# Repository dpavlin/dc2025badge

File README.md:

# DORS/CLUC Conference badge 2025

Conference page with badge instructions: [https://www.dorscluc.org/badge](https://www.dorscluc.org/badge/)

Build log: [https://hyperglitch.com/articles/dc2025-badge](https://hyperglitch.com/articles/dc2025-badge)

- `/hardware` - KiCad files for the badge
- `/firmware` - firmware for the badge
- `/3D` - 3D models for the stand, tag and programming jig
- `/notification_handler.py` - Python script for displaying the notifications and clock on the badge (in notifier mode)

----------------------------------------

This year’s badge has a number of functionalities, to be used both during and after the conference. During the conference the display can show your name (or any other text) and you also use it for quests. After the conference it can be used as a handy desktop notifier or a clock. And, of course, there’s a game available on it (not really Doom but it’s fast paced and action packed).

The badge contains a six character 9-segment display, logo shaped LED matrix, a NFC reader/writer, two buttons and a USB connection.

## How to set my own text?

The badge has six character alphanumeric display. It can show messages of up to 30 characters.

To set your custom text, hold the BTN1 for about three to five seconds until the badge switches to configuration mode. In that mode the BTN1 will move the cursor position while BTN2 will change the character under the cursor (hold it for fast character listing). To delete a character, select a space symbol (after number 9). To save the text hold the BTN1 again for three to five seconds until OK appears on screen.

## Quests? You said quests?

Yes! One is treasure hunt and another is badge hunt.

On the conference site there are nine hidden tags and your quest is to “collect” them all (tap them with your badge, please don’t physically take them). Each hidden tag will light up part of the logo on the badge. The first person who gets all of them will get a small reward.

Just like the last year’s badge which motivated attendants to interact with each other, this year’s badge also has an “interaction counter”. Put the antennas on two badges next to each other for a couple of seconds (it’s best to hold them both upwards and put antennas one over another so both screens could be seen) until both of them show the “NEW BADGE FOUND” text and they will exchange their details, incrementing the badge counter. NOTE: due to the power saving feature this might need to be repeated multiple times.

To check the current status of both quests press the BTN2 once or twice.

Note: in order to preserve the battery life, the NFC reader is in power save mode and it will activate when it detects a moving metal object nearby. Because of that sometimes it will be necessary to try the action (tapping the hidden tag or another badge) a couple of times.

## There are other modes?

I’m glad you asked. Yes, there are other modes on the badge:

- Conference mode scrolling text with quests)
- Clock (not really precise, needs configuration)
- Notifier (“passthrough” mode allowing you to set the screen over USB so it can be used as a desktop notifier)
- Game (a game!)
- Test (hardware test used during production)

To change the mode press and hold both buttons while powering on the badge. After a couple of seconds MODE will appear on screen. Use buttons to select the mode you like to try and press and hold both buttons for three to five seconds to confirm the selection.

## Configuration

When the badge is not in the notifier mode, some settings can be configured using the configuration menu available over USB connection. Connect the badge to computer (it probably won’t work on smartphone) and a new serial port will appear (/dev/ttyACM* on Linux, COM* on Windows). Connect to it either using some terminal program (miniterm, putty, screen, …) or even a web client such as the one available at https://www.anticyclone-systems.co.uk/aslwebterm.php (a Chromium based browser needs to be used as Firefox doesn’t support WebSerial). Make sure that Enter is set as CR+LF, click Connect and select your badge. Press Enter to redraw the menu. In case the Enter doesn’t work, try Ctrl+J.

## Notifier mode

When in notifier mode the serial terminal isn’t used for configuration but for the control. Each command must end ith a newline. Here are the commands:

- `S<some text>` will display that text on screen (for example “`Sshow this`”)
- `G<char_idx><segment_idx><1|0>` will control a specified character segment. `<char_idx>` is character index (0-5), `<segment_idx>` is the index of the segment (0-8) and `1|0` controls whether to turn the segment on or off. For example “`G161`” will turn on the middle horizontal segment on second character.
- `L<led_idx><1|0>` will turn the specified LED in the logo on or off. `<led_idx>` is in the range 00-39 (with leading zero). For example “`L021`” will turn on the led with index 2.
- `C` will clear the screen and LED matrix.
- `B<brightness>` will set the brightness where the `<brightness>` is in the rangge 00-99 (with leading zero). For example “`B05`” will set the brightness to 5%.

## License

ST middlewares and libraries are licensed under ST SLA0044 license. Shell menu is licensed under GPLv3. The rest of the code is licensed under MIT license.

The badge is designed by Igor Brkić from [https://hyperglitch.com](https://hyperglitch.com).

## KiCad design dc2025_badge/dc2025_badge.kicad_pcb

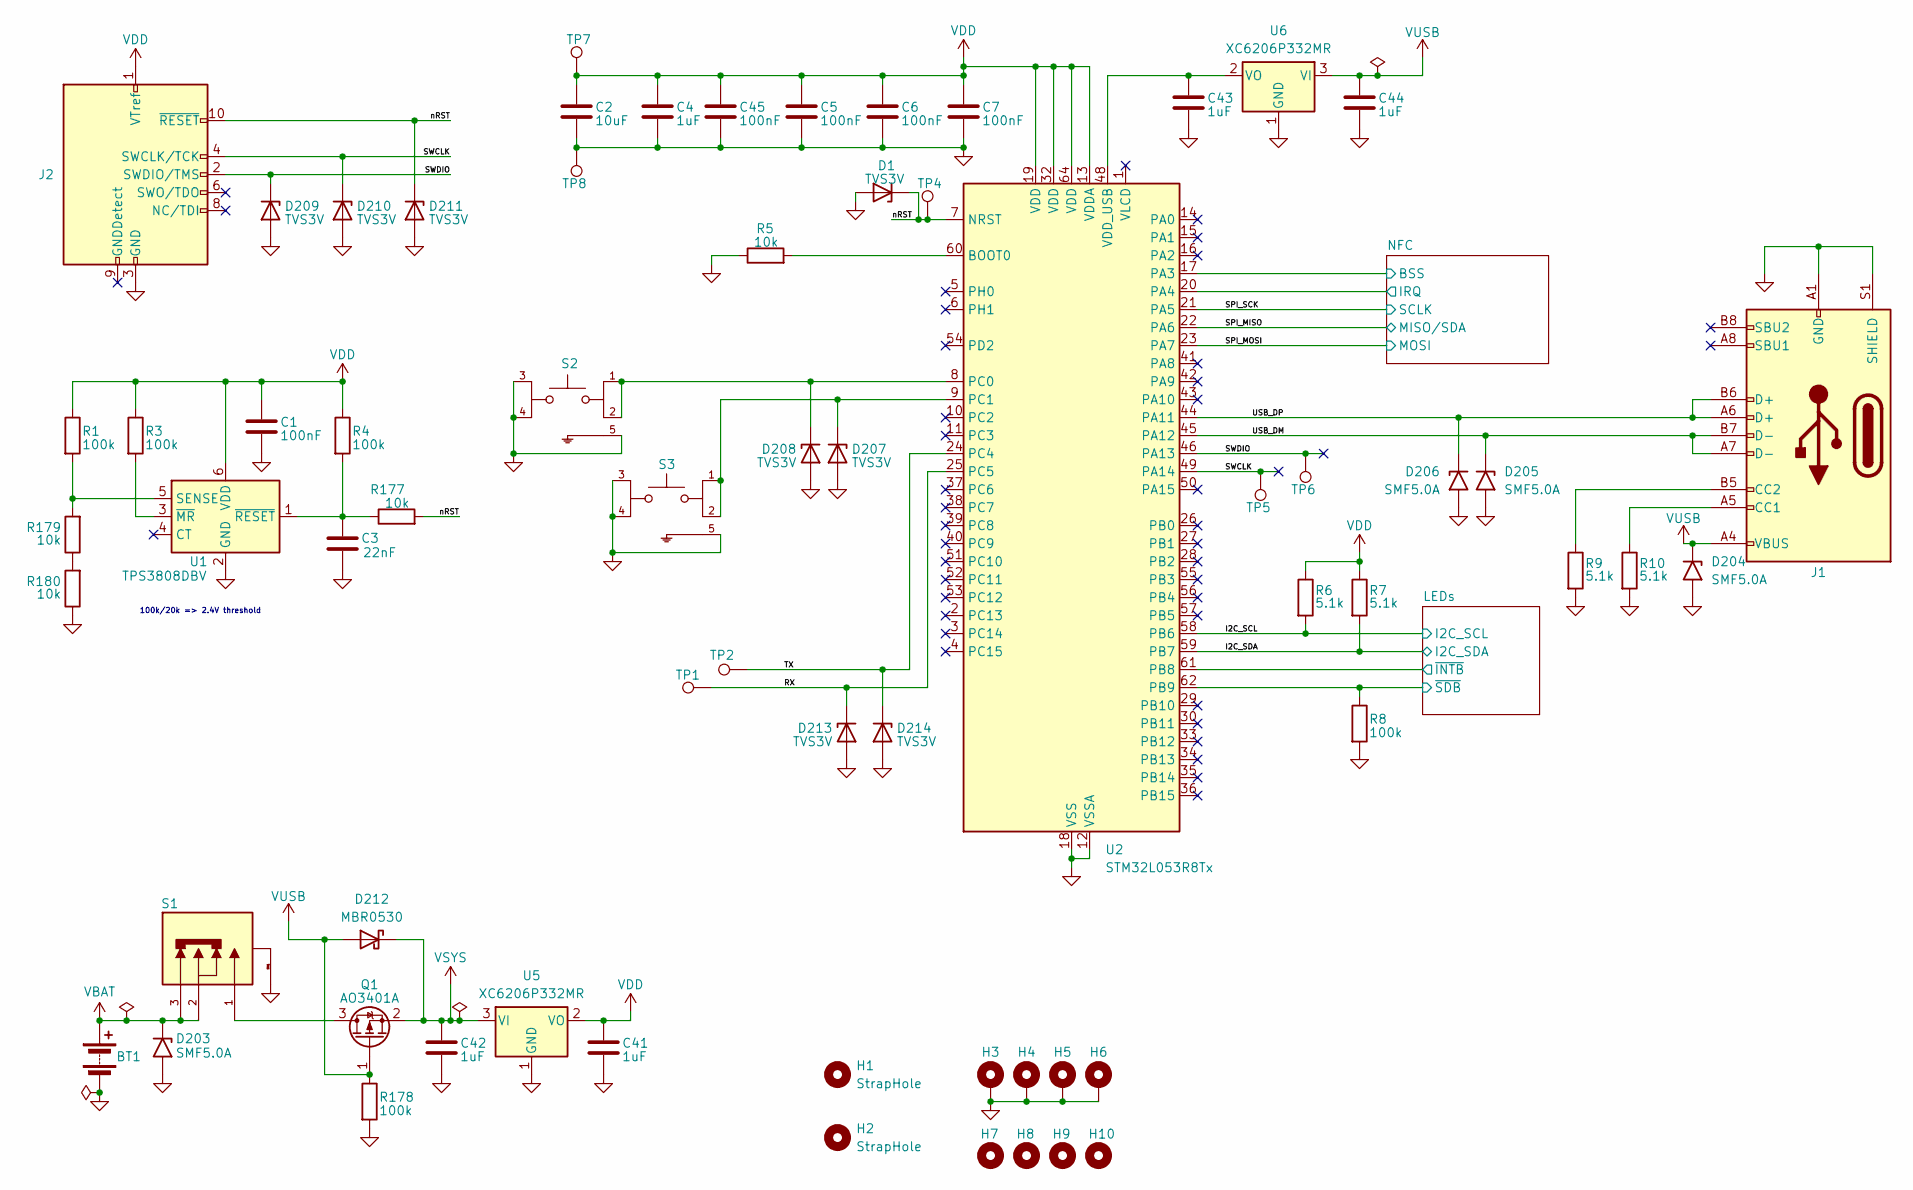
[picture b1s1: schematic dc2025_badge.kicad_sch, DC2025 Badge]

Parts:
BT1: Battery; keystone_2464
C1, C5, C6, C7, C45: 100nF; C_0402_1005Metric; MPN CL05B104KB54PNC; JLCPCB# C307331
C2: 10uF; C_0603_1608Metric; MPN GRM188Z71A106MA73D; JLCPCB# C237435
C3: 22nF; C_0402_1005Metric; MPN 0402B223K500NT; JLCPCB# C1532
C4, C41, C42, C43, C44: 1uF; C_0603_1608Metric; MPN 0603B105K250NT; JLCPCB# C59302
D1, D207, D208, D209, D210, D211, D213, D214: TVS3V; D_SOD-323; MPN SD03; JLCPCB# C502526
D203, D204, D205, D206: SMF5.0A; D_SMF; MPN SMF5.0A; JLCPCB# C19077497
D212: MBR0530; D_SOD-123; MPN MBR0530; JLCPCB# C475718
H1, H2: StrapHole; MountingHole_5mm
H3, H4, H5, H6: Cover nut; SMTSO3025CTJ; MPN C2916365; JLCPCB# C2916365
H7, H8, H9, H10: CoverMountingHole; MountingHole_3.2mm_M3_DIN965
J1: USB_C_Receptacle_USB2.0_16P; USB_C_Receptacle_GCT_USB4105-xx-A_16P_TopMnt_Horizontal; MPN TYPE-C-31-M-12; JLCPCB# C165948
J2: Conn_ARM_JTAG_SWD_10; Tag-Connect_TC2050-IDC-NL_2x05_P1.27mm_Vertical_with_bottom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
Q1: AO3401A; SOT-23; MPN AO3401A; JLCPCB# C15127
R1, R3, R4, R8, R178: 100k; R_0402_1005Metric; MPN 0402WGF1003TCE; JLCPCB# C25741
R5, R177, R179, R180: 10k; R_0402_1005Metric; MPN 0402WGF1002TCE; JLCPCB# C25744
R6, R7, R9, R10: 5.1k; R_0402_1005Metric; MPN 0402WGF5101TCE; JLCPCB# C25905
S1: SSSS811101; SW_SSSS811101; MPN SSSS811101; JLCPCB# C109335
S2, S3: SKHMQLE010; SW_SKHMQLE010; MPN SKHMQLE010; JLCPCB# C139767
TP1, TP2, TP4, TP5, TP6, TP7, TP8: TestPoint; TestPoint_Pad_D2.0mm
U1: TPS3808DBV; SOT-23-6; MPN TPS3808G01DBVR; JLCPCB# C19653
U2: STM32L053R8Tx; LQFP-64_10x10mm_P0.5mm; MPN STM32L053R8T6; JLCPCB# C79207
U5, U6: XC6206P332MR; SOT-23-3; MPN XC6206P332MR-G; JLCPCB# C5446

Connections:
/I2C_SCL: R6.2, U2.58 (PB6); also elsewhere on the board
/I2C_SDA: R7.2, U2.59 (PB7); also elsewhere on the board
/LEDs/~INTB: U2.61 (PB8); also elsewhere on the board
/LEDs/~SDB: R8.1, U2.62 (PB9); also elsewhere on the board
/NFC/BSS: U2.17 (PA3); also elsewhere on the board
/NFC/IRQ: U2.20 (PA4); also elsewhere on the board
/RX: D213.1 (K), TP1.1, U2.25 (PC5)
/SPI_MISO: U2.22 (PA6); also elsewhere on the board
/SPI_MOSI: U2.23 (PA7); also elsewhere on the board
/SPI_SCK: U2.21 (PA5); also elsewhere on the board
/SWCLK: D210.1 (K), J2.4 (SWCLK/TCK), TP5.1, U2.49 (PA14)
/SWDIO: D209.1 (K), J2.2 (SWDIO/TMS), TP6.1, U2.46 (PA13)
/TX: D214.1 (K), TP2.1, U2.24 (PC4)
/USB_DM: D205.1 (A1), J1.A7 (D-), J1.B7 (D-), U2.45 (PA12)
/USB_DP: D206.1 (A1), J1.A6 (D+), J1.B6 (D+), U2.44 (PA11)
/nRST: D1.1 (K), D211.1 (K), J2.10 (~RESET), R177.2, TP4.1, U2.7 (NRST)
GND: BT1.2 (-), C1.2, C2.2, C3.2, C4.2, C5.2, C6.2, C7.2, C41.2, C42.2, C43.2, C44.2, C45.2, D1.2 (A), D203.2 (A2), D204.2 (A2), D205.2 (A2), D206.2 (A2), D207.2 (A), D208.2 (A), D209.2 (A), D210.2 (A), D211.2 (A), D213.2 (A), D214.2 (A), H3.1, H4.1, H5.1, H6.1, J1.A1 (GND), J1.A12 (GND), J1.B1 (GND), J1.B12 (GND), J1.S1 (SHIELD), J2.3 (GND), J2.5 (GND), R5.1, R8.2, R9.2, R10.2, R178.2, R180.1, S1.SH1, S1.SH2, S1.SH3, S1.SH4, S2.3, S2.4, S2.5, S3.3, S3.4, S3.5, TP8.1, U1.2 (GND), U2.12 (VSSA), U2.18 (VSS), U2.31 (VSS), U2.47 (VSS), U2.63 (VSS), U5.1 (GND), U6.1 (GND); also elsewhere on the board
unnamed: D207.1 (K), S3.1, S3.2, U2.9 (PC1)
unnamed: D208.1 (K), S2.1, S2.2, U2.8 (PC0)
unnamed: J1.A5 (CC1), R10.1
unnamed: J1.B5 (CC2), R9.1
unnamed: Q1.3 (D), S1.1
unnamed: R179.1, R180.2
unnamed: R1.2, R179.2, U1.5 (SENSE)
unnamed: R3.2, U1.3 (~MR)
unnamed: C3.1, R4.2, R177.1, U1.1 (~RESET)
unnamed: R5.2, U2.60 (BOOT0)
unnamed: C43.1, U2.48 (VDD_USB), U6.2 (VO)
VBAT: BT1.1 (+), D203.1 (A1), S1.2, S1.3
VDD: C1.1, C2.1, C4.1, C5.1, C6.1, C7.1, C41.1, C45.1, J2.1 (VTref), R1.1, R3.1, R4.1, R6.1, R7.1, TP7.1, U1.6 (VDD), U2.13 (VDDA), U2.19 (VDD), U2.32 (VDD), U2.64 (VDD), U5.2 (VO); also elsewhere on the board
VSYS: C42.1, D212.1 (K), Q1.2 (S), U5.3 (VI); also elsewhere on the board
VUSB: C44.1, D204.1 (A1), D212.2 (A), J1.A4 (VBUS), J1.A9 (VBUS), J1.B4 (VBUS), J1.B9 (VBUS), Q1.1 (G), R178.1, U6.3 (VI)

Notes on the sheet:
100k/20k => 2.4V threshold

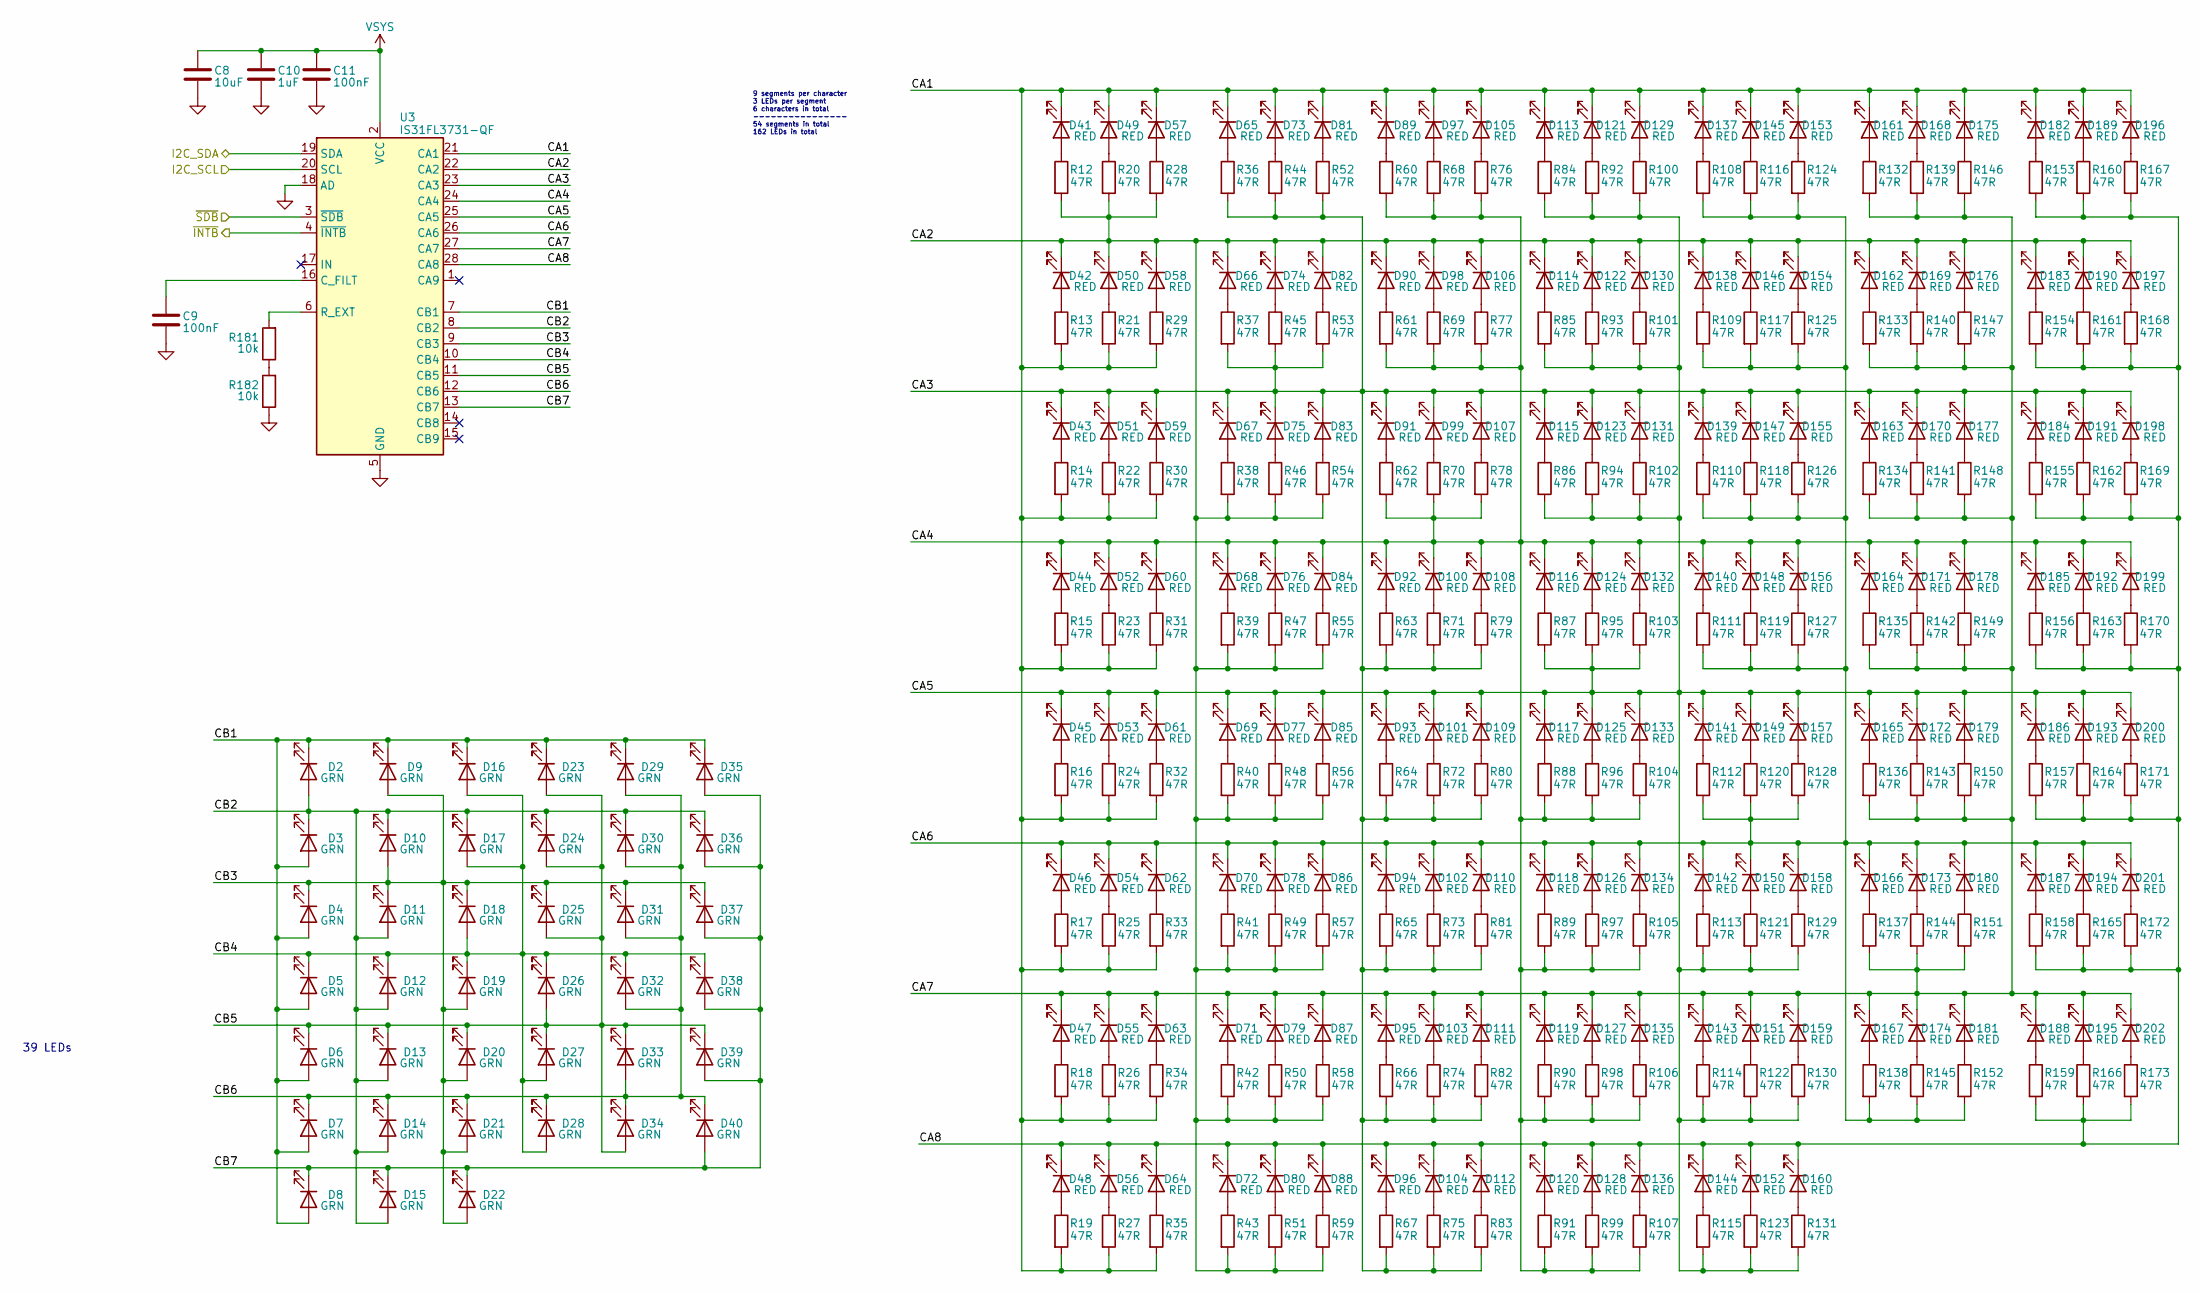
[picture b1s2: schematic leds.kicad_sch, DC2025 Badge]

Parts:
C8: 10uF; C_0603_1608Metric; MPN GRM188Z71A106MA73D; JLCPCB# C237435
C9, C11: 100nF; C_0402_1005Metric; MPN CL05B104KB54PNC; JLCPCB# C307331
C10: 1uF; C_0603_1608Metric; MPN 0603B105K250NT; JLCPCB# C59302
D2, D3, D4, D5, D6, D7, D8, D9, D10, D11, D12, D13, D14, D15, D16, D17, D18, D19, D20, D21, D22, D23, D24, D25, D26, D27, D28, D29, D30, D31, D32, D33, D34, D35, D36, D37, D38, D39, D40: GRN; LED_0603_1608Metric; MPN XL-1608UGC-04; JLCPCB# C965804
D41, D42, D43, D44, D45, D46, D47, D48, D49, D50, D51, D52, D53, D54, D55, D56, D57, D58, D59, D60, D61, D62, D63, D64, D65, D66, D67, D68, D69, D70, D71, D72, D73, D74, D75, D76, D77, D78, D79, D80, D81, D82, D83, D84, D85, D86, D87, D88, D89, D90, D91, D92, D93, D94, D95, D96, D97, D98, D99, D100, D101, D102, D103, D104, D105, D106, D107, D108, D109, D110, D111, D112, D113, D114, D115, D116, D117, D118, D119, D120, D121, D122, D123, D124, D125, D126, D127, D128, D129, D130, D131, D132, D133, D134, D135, D136, D137, D138, D139, D140, D141, D142, D143, D144, D145, D146, D147, D148, D149, D150, D151, D152, D153, D154, D155, D156, D157, D158, D159, D160, D161, D162, D163, D164, D165, D166, D167, D168, D169, D170, D171, D172, D173, D174, D175, D176, D177, D178, D179, D180, D181, D182, D183, D184, D185, D186, D187, D188, D189, D190, D191, D192, D193, D194, D195, D196, D197, D198, D199, D200, D201, D202: RED; LED_0603_1608Metric; MPN XL-1608SURC-06; JLCPCB# C965799
R12, R13, R14, R15, R16, R17, R18, R19, R20, R21, R22, R23, R24, R25, R26, R27, R28, R29, R30, R31, R32, R33, R34, R35, R36, R37, R38, R39, R40, R41, R42, R43, R44, R45, R46, R47, R48, R49, R50, R51, R52, R53, R54, R55, R56, R57, R58, R59, R60, R61, R62, R63, R64, R65, R66, R67, R68, R69, R70, R71, R72, R73, R74, R75, R76, R77, R78, R79, R80, R81, R82, R83, R84, R85, R86, R87, R88, R89, R90, R91, R92, R93, R94, R95, R96, R97, R98, R99, R100, R101, R102, R103, R104, R105, R106, R107, R108, R109, R110, R111, R112, R113, R114, R115, R116, R117, R118, R119, R120, R121, R122, R123, R124, R125, R126, R127, R128, R129, R130, R131, R132, R133, R134, R135, R136, R137, R138, R139, R140, R141, R142, R143, R144, R145, R146, R147, R148, R149, R150, R151, R152, R153, R154, R155, R156, R157, R158, R159, R160, R161, R162, R163, R164, R165, R166, R167, R168, R169, R170, R171, R172, R173: 47R; R_0402_1005Metric; MPN 0402WGF470JTCE; JLCPCB# C25118
R181, R182: 10k; R_0402_1005Metric; MPN 0402WGF1002TCE; JLCPCB# C25744
U3: IS31FL3731-QF; QFN-28-1EP_4x4mm_P0.4mm_EP2.3x2.3mm; MPN IS31FL3731-QFLS2-TR; JLCPCB# C191206

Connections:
/I2C_SCL: U3.20 (SCL); also elsewhere on the board
/I2C_SDA: U3.19 (SDA); also elsewhere on the board
/LEDs/CA1: D41.1 (K), D49.1 (K), D57.1 (K), D65.1 (K), D73.1 (K), D81.1 (K), D89.1 (K), D97.1 (K), D105.1 (K), D113.1 (K), D121.1 (K), D129.1 (K), D137.1 (K), D145.1 (K), D153.1 (K), D161.1 (K), D168.1 (K), D175.1 (K), D182.1 (K), D189.1 (K), D196.1 (K), R13.2, R14.2, R15.2, R16.2, R17.2, R18.2, R19.2, R21.2, R22.2, R23.2, R24.2, R25.2, R26.2, R27.2, R29.2, R30.2, R31.2, R32.2, R33.2, R34.2, R35.2, U3.21 (CA1)
/LEDs/CA2: D42.1 (K), D50.1 (K), D58.1 (K), D66.1 (K), D74.1 (K), D82.1 (K), D90.1 (K), D98.1 (K), D106.1 (K), D114.1 (K), D122.1 (K), D130.1 (K), D138.1 (K), D146.1 (K), D154.1 (K), D162.1 (K), D169.1 (K), D176.1 (K), D183.1 (K), D190.1 (K), D197.1 (K), R12.2, R20.2, R28.2, R38.2, R39.2, R40.2, R41.2, R42.2, R43.2, R46.2, R47.2, R48.2, R49.2, R50.2, R51.2, R54.2, R55.2, R56.2, R57.2, R58.2, R59.2, U3.22 (CA2)
/LEDs/CA3: D43.1 (K), D51.1 (K), D59.1 (K), D67.1 (K), D75.1 (K), D83.1 (K), D91.1 (K), D99.1 (K), D107.1 (K), D115.1 (K), D123.1 (K), D131.1 (K), D139.1 (K), D147.1 (K), D155.1 (K), D163.1 (K), D170.1 (K), D177.1 (K), D184.1 (K), D191.1 (K), D198.1 (K), R36.2, R37.2, R44.2, R45.2, R52.2, R53.2, R63.2, R64.2, R65.2, R66.2, R67.2, R71.2, R72.2, R73.2, R74.2, R75.2, R79.2, R80.2, R81.2, R82.2, R83.2, U3.23 (CA3)
/LEDs/CA4: D44.1 (K), D52.1 (K), D60.1 (K), D68.1 (K), D76.1 (K), D84.1 (K), D92.1 (K), D100.1 (K), D108.1 (K), D116.1 (K), D124.1 (K), D132.1 (K), D140.1 (K), D148.1 (K), D156.1 (K), D164.1 (K), D171.1 (K), D178.1 (K), D185.1 (K), D192.1 (K), D199.1 (K), R60.2, R61.2, R62.2, R68.2, R69.2, R70.2, R76.2, R77.2, R78.2, R88.2, R89.2, R90.2, R91.2, R96.2, R97.2, R98.2, R99.2, R104.2, R105.2, R106.2, R107.2, U3.24 (CA4)
/LEDs/CA5: D45.1 (K), D53.1 (K), D61.1 (K), D69.1 (K), D77.1 (K), D85.1 (K), D93.1 (K), D101.1 (K), D109.1 (K), D117.1 (K), D125.1 (K), D133.1 (K), D141.1 (K), D149.1 (K), D157.1 (K), D165.1 (K), D172.1 (K), D179.1 (K), D186.1 (K), D193.1 (K), D200.1 (K), R84.2, R85.2, R86.2, R87.2, R92.2, R93.2, R94.2, R95.2, R100.2, R101.2, R102.2, R103.2, R113.2, R114.2, R115.2, R121.2, R122.2, R123.2, R129.2, R130.2, R131.2, U3.25 (CA5)
/LEDs/CA6: D46.1 (K), D54.1 (K), D62.1 (K), D70.1 (K), D78.1 (K), D86.1 (K), D94.1 (K), D102.1 (K), D110.1 (K), D118.1 (K), D126.1 (K), D134.1 (K), D142.1 (K), D150.1 (K), D158.1 (K), D166.1 (K), D173.1 (K), D180.1 (K), D187.1 (K), D194.1 (K), D201.1 (K), R108.2, R109.2, R110.2, R111.2, R112.2, R116.2, R117.2, R118.2, R119.2, R120.2, R124.2, R125.2, R126.2, R127.2, R128.2, R138.2, R145.2, R152.2, U3.26 (CA6)
/LEDs/CA7: D47.1 (K), D55.1 (K), D63.1 (K), D71.1 (K), D79.1 (K), D87.1 (K), D95.1 (K), D103.1 (K), D111.1 (K), D119.1 (K), D127.1 (K), D135.1 (K), D143.1 (K), D151.1 (K), D159.1 (K), D167.1 (K), D174.1 (K), D181.1 (K), D188.1 (K), D195.1 (K), D202.1 (K), R132.2, R133.2, R134.2, R135.2, R136.2, R137.2, R139.2, R140.2, R141.2, R142.2, R143.2, R144.2, R146.2, R147.2, R148.2, R149.2, R150.2, R151.2, U3.27 (CA7)
/LEDs/CA8: D48.1 (K), D56.1 (K), D64.1 (K), D72.1 (K), D80.1 (K), D88.1 (K), D96.1 (K), D104.1 (K), D112.1 (K), D120.1 (K), D128.1 (K), D136.1 (K), D144.1 (K), D152.1 (K), D160.1 (K), R153.2, R154.2, R155.2, R156.2, R157.2, R158.2, R159.2, R160.2, R161.2, R162.2, R163.2, R164.2, R165.2, R166.2, R167.2, R168.2, R169.2, R170.2, R171.2, R172.2, R173.2, U3.28 (CA8)
/LEDs/CB1: D2.1 (K), D3.2 (A), D4.2 (A), D5.2 (A), D6.2 (A), D7.2 (A), D8.2 (A), D9.1 (K), D16.1 (K), D23.1 (K), D29.1 (K), D35.1 (K), U3.7 (CB1)
/LEDs/CB2: D2.2 (A), D3.1 (K), D10.1 (K), D11.2 (A), D12.2 (A), D13.2 (A), D14.2 (A), D15.2 (A), D17.1 (K), D24.1 (K), D30.1 (K), D36.1 (K), U3.8 (CB2)
/LEDs/CB3: D4.1 (K), D9.2 (A), D10.2 (A), D11.1 (K), D18.1 (K), D19.2 (A), D20.2 (A), D21.2 (A), D22.2 (A), D25.1 (K), D31.1 (K), D37.1 (K), U3.9 (CB3)
/LEDs/CB4: D5.1 (K), D12.1 (K), D16.2 (A), D17.2 (A), D18.2 (A), D19.1 (K), D26.1 (K), D27.2 (A), D28.2 (A), D32.1 (K), D38.1 (K), U3.10 (CB4)
/LEDs/CB5: D6.1 (K), D13.1 (K), D20.1 (K), D23.2 (A), D24.2 (A), D25.2 (A), D26.2 (A), D27.1 (K), D33.1 (K), D34.2 (A), D39.1 (K), U3.11 (CB5)
/LEDs/CB6: D7.1 (K), D14.1 (K), D21.1 (K), D28.1 (K), D29.2 (A), D30.2 (A), D31.2 (A), D32.2 (A), D33.2 (A), D34.1 (K), D40.1 (K), U3.12 (CB6)
/LEDs/CB7: D8.1 (K), D15.1 (K), D22.1 (K), D35.2 (A), D36.2 (A), D37.2 (A), D38.2 (A), D39.2 (A), D40.2 (A), U3.13 (CB7)
/LEDs/~INTB: U3.4 (~INTB); also elsewhere on the board
/LEDs/~SDB: U3.3 (~SDB); also elsewhere on the board
GND: C8.2, C9.2, C10.2, C11.2, R182.1, U3.5 (GND), U3.18 (AD), U3.29 (GND); also elsewhere on the board
unnamed: D41.2 (A), R12.1
unnamed: D42.2 (A), R13.1
unnamed: D43.2 (A), R14.1
unnamed: D44.2 (A), R15.1
unnamed: D45.2 (A), R16.1
unnamed: D46.2 (A), R17.1
unnamed: D47.2 (A), R18.1
unnamed: D48.2 (A), R19.1
unnamed: D49.2 (A), R20.1
unnamed: D50.2 (A), R21.1
unnamed: D51.2 (A), R22.1
unnamed: D52.2 (A), R23.1
unnamed: D53.2 (A), R24.1
unnamed: D54.2 (A), R25.1
unnamed: D55.2 (A), R26.1
unnamed: D56.2 (A), R27.1
unnamed: D57.2 (A), R28.1
unnamed: D58.2 (A), R29.1
unnamed: D59.2 (A), R30.1
unnamed: D60.2 (A), R31.1
unnamed: D61.2 (A), R32.1
unnamed: D62.2 (A), R33.1
unnamed: D63.2 (A), R34.1
unnamed: D64.2 (A), R35.1
unnamed: D65.2 (A), R36.1
unnamed: D66.2 (A), R37.1
unnamed: D67.2 (A), R38.1
unnamed: D68.2 (A), R39.1
unnamed: D69.2 (A), R40.1
unnamed: D70.2 (A), R41.1
unnamed: D71.2 (A), R42.1
unnamed: D72.2 (A), R43.1
unnamed: D73.2 (A), R44.1
unnamed: D74.2 (A), R45.1
unnamed: D75.2 (A), R46.1
unnamed: D76.2 (A), R47.1
unnamed: D77.2 (A), R48.1
unnamed: D78.2 (A), R49.1
unnamed: D79.2 (A), R50.1
unnamed: D80.2 (A), R51.1
unnamed: D81.2 (A), R52.1
unnamed: D82.2 (A), R53.1
unnamed: D83.2 (A), R54.1
unnamed: D84.2 (A), R55.1
unnamed: D85.2 (A), R56.1
unnamed: D86.2 (A), R57.1
unnamed: D87.2 (A), R58.1
unnamed: D88.2 (A), R59.1
unnamed: D89.2 (A), R60.1
unnamed: D90.2 (A), R61.1
unnamed: D91.2 (A), R62.1
unnamed: D92.2 (A), R63.1
unnamed: D93.2 (A), R64.1
unnamed: D94.2 (A), R65.1
unnamed: D95.2 (A), R66.1
unnamed: D96.2 (A), R67.1
unnamed: D97.2 (A), R68.1
unnamed: D98.2 (A), R69.1
unnamed: D99.2 (A), R70.1
unnamed: D100.2 (A), R71.1
unnamed: D101.2 (A), R72.1
unnamed: D102.2 (A), R73.1
unnamed: D103.2 (A), R74.1
unnamed: D104.2 (A), R75.1
unnamed: D105.2 (A), R76.1
unnamed: D106.2 (A), R77.1
unnamed: D107.2 (A), R78.1
unnamed: D108.2 (A), R79.1
unnamed: D109.2 (A), R80.1
unnamed: D110.2 (A), R81.1
unnamed: D111.2 (A), R82.1
unnamed: D112.2 (A), R83.1
unnamed: D113.2 (A), R84.1
unnamed: D114.2 (A), R85.1
unnamed: D115.2 (A), R86.1
unnamed: D116.2 (A), R87.1
unnamed: D117.2 (A), R88.1
unnamed: D118.2 (A), R89.1
unnamed: D119.2 (A), R90.1
unnamed: D120.2 (A), R91.1
unnamed: D121.2 (A), R92.1
unnamed: D122.2 (A), R93.1
unnamed: D123.2 (A), R94.1
unnamed: D124.2 (A), R95.1
unnamed: D125.2 (A), R96.1
unnamed: D126.2 (A), R97.1
unnamed: D127.2 (A), R98.1
unnamed: D128.2 (A), R99.1
unnamed: D129.2 (A), R100.1
unnamed: D130.2 (A), R101.1
unnamed: D131.2 (A), R102.1
unnamed: D132.2 (A), R103.1
unnamed: D133.2 (A), R104.1
unnamed: D134.2 (A), R105.1
unnamed: D135.2 (A), R106.1
unnamed: D136.2 (A), R107.1
unnamed: D137.2 (A), R108.1
unnamed: D138.2 (A), R109.1
unnamed: D139.2 (A), R110.1
unnamed: D140.2 (A), R111.1
unnamed: D141.2 (A), R112.1
unnamed: D142.2 (A), R113.1
unnamed: D143.2 (A), R114.1
unnamed: D144.2 (A), R115.1
unnamed: D145.2 (A), R116.1
unnamed: D146.2 (A), R117.1
unnamed: D147.2 (A), R118.1
unnamed: D148.2 (A), R119.1
unnamed: D149.2 (A), R120.1
unnamed: D150.2 (A), R121.1
unnamed: D151.2 (A), R122.1
unnamed: D152.2 (A), R123.1
unnamed: D153.2 (A), R124.1
unnamed: D154.2 (A), R125.1
unnamed: D155.2 (A), R126.1
unnamed: D156.2 (A), R127.1
unnamed: D157.2 (A), R128.1
unnamed: D158.2 (A), R129.1
unnamed: D159.2 (A), R130.1
unnamed: D160.2 (A), R131.1
unnamed: D161.2 (A), R132.1
unnamed: D162.2 (A), R133.1
unnamed: D163.2 (A), R134.1
unnamed: D164.2 (A), R135.1
unnamed: D165.2 (A), R136.1
unnamed: D166.2 (A), R137.1
unnamed: D167.2 (A), R138.1
unnamed: D168.2 (A), R139.1
unnamed: D169.2 (A), R140.1
unnamed: D170.2 (A), R141.1
unnamed: D171.2 (A), R142.1
unnamed: D172.2 (A), R143.1
unnamed: D173.2 (A), R144.1
unnamed: D174.2 (A), R145.1
unnamed: D175.2 (A), R146.1
unnamed: D176.2 (A), R147.1
unnamed: D177.2 (A), R148.1
unnamed: D178.2 (A), R149.1
unnamed: D179.2 (A), R150.1
unnamed: D180.2 (A), R151.1
unnamed: D181.2 (A), R152.1
unnamed: D182.2 (A), R153.1
unnamed: D183.2 (A), R154.1
unnamed: D184.2 (A), R155.1
unnamed: D185.2 (A), R156.1
unnamed: D186.2 (A), R157.1
unnamed: D187.2 (A), R158.1
unnamed: D188.2 (A), R159.1
unnamed: D189.2 (A), R160.1
unnamed: D190.2 (A), R161.1
unnamed: D191.2 (A), R162.1
unnamed: D192.2 (A), R163.1
unnamed: D193.2 (A), R164.1
unnamed: D194.2 (A), R165.1
unnamed: D195.2 (A), R166.1
unnamed: D196.2 (A), R167.1
unnamed: D197.2 (A), R168.1
unnamed: D198.2 (A), R169.1
unnamed: D199.2 (A), R170.1
unnamed: D200.2 (A), R171.1
unnamed: D201.2 (A), R172.1
unnamed: D202.2 (A), R173.1
unnamed: R181.1, R182.2
unnamed: C9.1, U3.16 (C_FILT)
unnamed: R181.2, U3.6 (R_EXT)
VSYS: C8.1, C10.1, C11.1, U3.2 (VCC); also elsewhere on the board

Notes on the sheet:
9 segments per character 3 LEDs per segment 6 characters in total ---------------- 54 segments in total 162 LEDs in total
39 LEDs

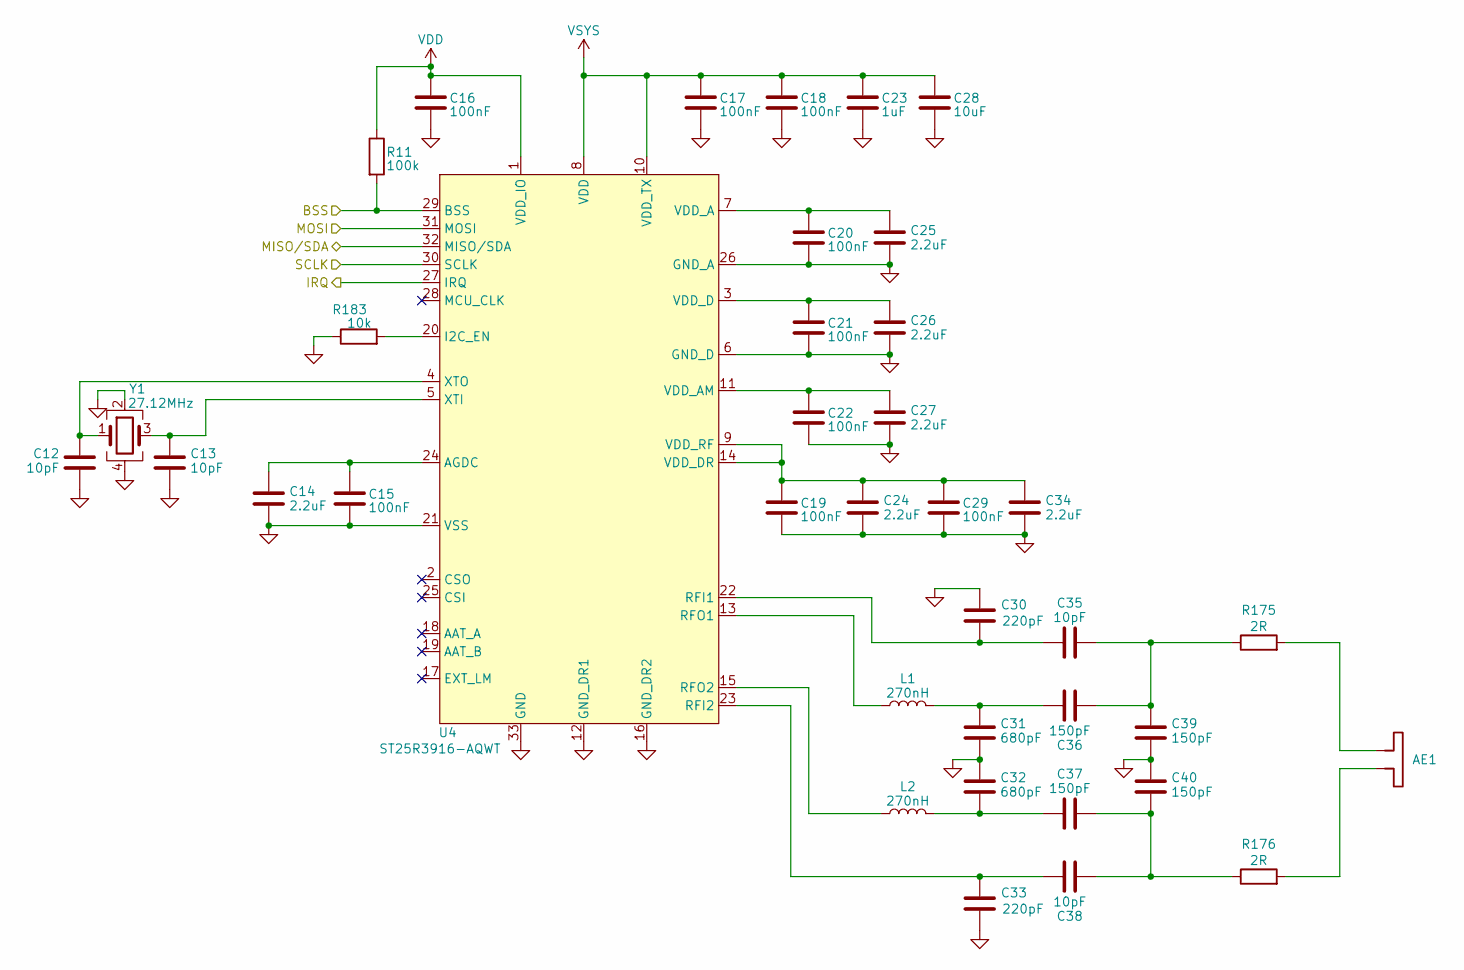
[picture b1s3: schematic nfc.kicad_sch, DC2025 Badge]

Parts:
AE1: Antenna; nfc_antenna
C12, C13, C35, C38: 10pF; C_0402_1005Metric; MPN CL05C100JB5NNNC; JLCPCB# C32949
C14, C24, C25, C26, C27, C34: 2.2uF; C_0603_1608Metric; MPN CL10A225KO8NNNC; JLCPCB# C23630
C15, C16, C17, C18, C19, C20, C21, C22, C29: 100nF; C_0402_1005Metric; MPN CL05B104KB54PNC; JLCPCB# C307331
C23: 1uF; C_0603_1608Metric; MPN 0603B105K250NT; JLCPCB# C59302
C28: 10uF; C_0603_1608Metric; MPN GRM188Z71A106MA73D; JLCPCB# C237435
C30, C33: 220pF; C_0402_1005Metric; MPN 0402B221K500NT; JLCPCB# C1530
C31, C32: 680pF; C_0402_1005Metric; MPN 0402B681K500NT; JLCPCB# C1541
C36, C37, C39, C40: 150pF; C_0402_1005Metric; MPN 0402B151K500NT; JLCPCB# C1527
L1, L2: 270nH; L_0402_1005Metric_Pad0.77x0.64mm_HandSolder; MPN LQB15NNR27K10D; JLCPCB# C907954
R11: 100k; R_0402_1005Metric; MPN 0402WGF1003TCE; JLCPCB# C25741
R175, R176: 2R; R_0402_1005Metric; MPN WR04X2R0JTL; JLCPCB# C170397
R183: 10k; R_0402_1005Metric; MPN 0402WGF1002TCE; JLCPCB# C25744
U4: ST25R3916-AQWT; UFQFPN-32-1EP_5x5mm_P0.5mm_EP3.5x3.5mm; MPN ST25R3916-AQWT; JLCPCB# C2908147
Y1: 27.12MHz; Crystal_SMD_3225-4Pin_3.2x2.5mm; MPN X32252712MMB4SI; JLCPCB# C29975

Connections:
/NFC/BSS: R11.2, U4.29 (BSS); also elsewhere on the board
/NFC/IRQ: U4.27 (IRQ); also elsewhere on the board
/SPI_MISO: U4.32 (MISO/SDA); also elsewhere on the board
/SPI_MOSI: U4.31 (MOSI); also elsewhere on the board
/SPI_SCK: U4.30 (SCLK); also elsewhere on the board
GND: C12.1, C13.1, C14.2, C15.2, C16.2, C17.2, C18.2, C19.2, C20.2, C21.2, C22.2, C23.2, C24.2, C25.2, C26.2, C27.2, C28.2, C29.2, C30.2, C31.2, C32.1, C33.1, C34.2, C39.2, C40.1, R183.1, U4.6 (GND_D), U4.12 (GND_DR1), U4.16 (GND_DR2), U4.21 (VSS), U4.26 (GND_A), U4.33 (GND), Y1.2, Y1.4; also elsewhere on the board
unnamed: AE1.1, R175.2
unnamed: AE1.2, R176.2
unnamed: C31.1, C36.1, L1.2
unnamed: C32.2, C37.1, L2.2
unnamed: C35.2, C36.2, C39.1, R175.1
unnamed: C37.2, C38.2, C40.2, R176.1
unnamed: C14.1, C15.1, U4.24 (AGDC)
unnamed: R183.2, U4.20 (I2C_EN)
unnamed: C30.1, C35.1, U4.22 (RFI1)
unnamed: C33.2, C38.1, U4.23 (RFI2)
unnamed: L1.1, U4.13 (RFO1)
unnamed: L2.1, U4.15 (RFO2)
unnamed: C20.1, C25.1, U4.7 (VDD_A)
unnamed: C22.1, C27.1, U4.11 (VDD_AM)
unnamed: C21.1, C26.1, U4.3 (VDD_D)
unnamed: C19.1, C24.1, C29.1, C34.1, U4.9 (VDD_RF), U4.14 (VDD_DR)
unnamed: C13.2, U4.5 (XTI), Y1.3
unnamed: C12.2, U4.4 (XTO), Y1.1
VDD: C16.1, R11.1, U4.1 (VDD_IO); also elsewhere on the board
VSYS: C17.1, C18.1, C23.1, C28.1, U4.8 (VDD), U4.10 (VDD_TX); also elsewhere on the board

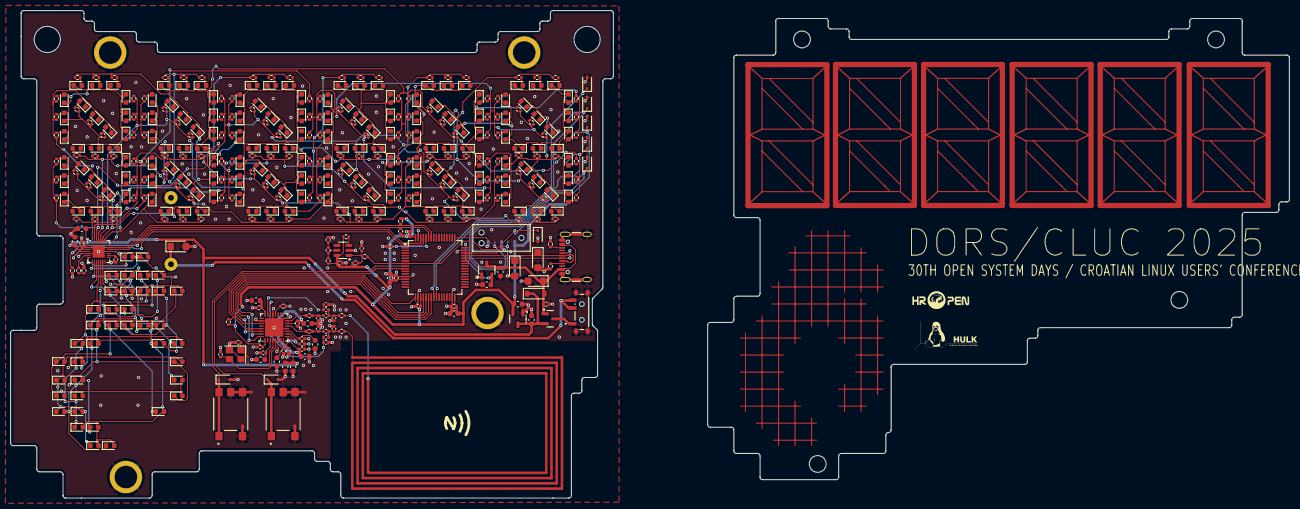
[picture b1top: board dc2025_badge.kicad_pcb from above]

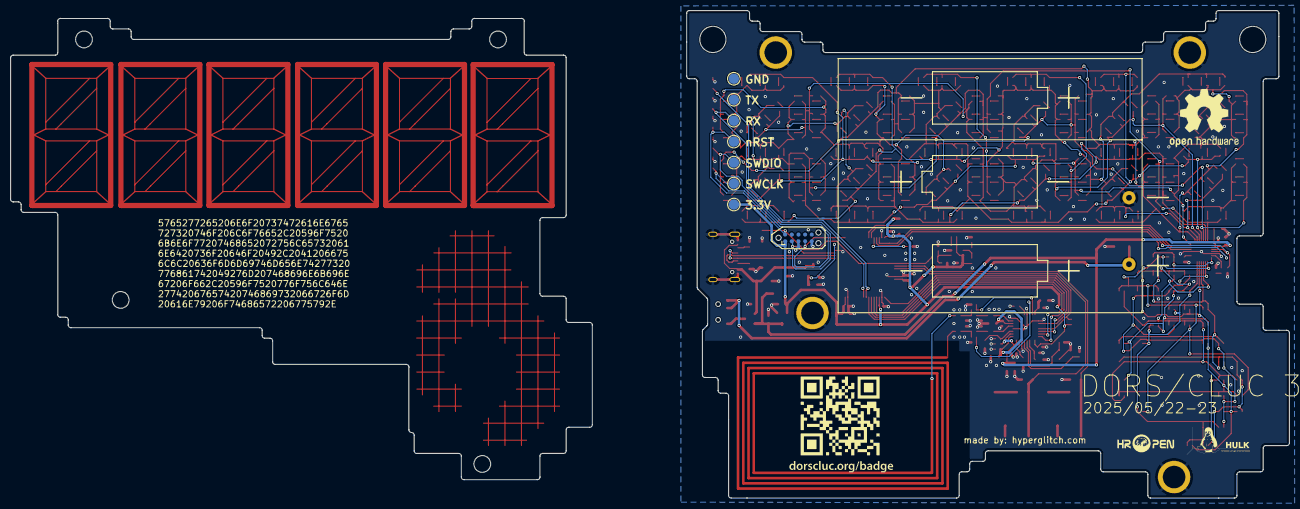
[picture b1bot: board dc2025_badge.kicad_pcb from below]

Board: 2 copper layers, 244.0 x 93.0 mm, 474 parts (9 on the bottom side), 230 nets.

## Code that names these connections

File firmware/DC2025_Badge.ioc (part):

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Mcu.Name=STM32L073R(B-Z)Tx
Mcu.Package=LQFP64
Mcu.UserName=STM32L073RBTx
PA11.Mode=Device
PA11.Signal=USB_DM
PA12.Mode=Device
PA12.Signal=USB_DP
PA13.Mode=Serial_Wire
PA13.Signal=SYS_SWDIO
PA14.Mode=Serial_Wire
PA14.Signal=SYS_SWCLK
PA3.GPIOParameters=GPIO_Label
PA3.GPIO_Label=NFC_BSS
PA3.Signal=GPIO_Output
PA4.GPIOParameters=GPIO_Label
PA4.GPIO_Label=NFC_IRQ
PA4.Signal=GPXTI4
PA5.Mode=Full_Duplex_Master
PA5.Signal=SPI1_SCK
PA6.Mode=Full_Duplex_Master
PA6.Signal=SPI1_MISO
PA7.Mode=Full_Duplex_Master
PA7.Signal=SPI1_MOSI
PB14.Signal=GPIO_Output
PB15.Signal=GPIO_Output
PB6.Mode=I2C
PB6.Signal=I2C1_SCL
PB7.Mode=I2C
PB7.Signal=I2C1_SDA
PB8.GPIOParameters=GPIO_Label
PB8.GPIO_Label=LED_NINT
PB8.Signal=GPXTI8
PB9.GPIOParameters=GPIO_Label
PB9.GPIO_Label=LED_NSD
PB9.Signal=GPIO_Output
PC0.GPIOParameters=GPIO_PuPd,GPIO_Label,GPIO_ModeDefaultEXTI
PC0.GPIO_Label=BUTTON0
PC0.GPIO_ModeDefaultEXTI=GPIO_MODE_IT_RISING_FALLING
PC0.GPIO_PuPd=GPIO_PULLUP
PC0.Signal=GPXTI0
PC1.GPIOParameters=GPIO_PuPd,GPIO_Label,GPIO_ModeDefaultEXTI
PC1.GPIO_Label=BUTTON1ALT
PC1.GPIO_ModeDefaultEXTI=GPIO_MODE_IT_RISING_FALLING
PC1.GPIO_PuPd=GPIO_PULLUP
PC1.Signal=GPXTI1
PC2.GPIOParameters=GPIO_PuPd,GPIO_Label,GPIO_ModeDefaultEXTI
PC2.GPIO_Label=BUTTON1
PC2.GPIO_ModeDefaultEXTI=GPIO_MODE_IT_RISING_FALLING
PC2.GPIO_PuPd=GPIO_PULLUP
PC2.Signal=GPXTI2
PC4.Mode=Asynchronous
PC4.Signal=LPUART1_TX
PC5.Mode=Asynchronous
PC5.Signal=LPUART1_RX
PC6.Signal=GPIO_Output
PC7.Signal=GPIO_Output
PC8.Signal=GPIO_Output
PC9.Signal=GPIO_Output
RCC.HSE_VALUE=8000000
RCC.SYSCLKFreq_VALUE=16000000
RCC.SYSCLKSource=RCC_SYSCLKSOURCE_HSI
board=custom

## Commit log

2025-03-18 initial prototype, 0402 leds
2025-03-19 0603 leds added, prototype version finished
2025-03-19 add helper scripts
2025-03-19 add production files for first prototype
2025-05-16 hardware added production version
2025-05-20 rename hardware folder
2025-05-22 add firmware code
2025-05-22 add 3D files
2025-05-22 add README
2025-05-22 add simple notification processing script
2025-05-30 fix warnings
2025-05-30 add brightness to notifier mode (doesn't work)
2025-05-30 ioc file update
2025-05-30 update license for shell menu
2025-05-30 add page content to readme
2025-05-30 readme update
2025-05-30 notification_handler: show clock when there are no notifications
2025-05-31 brightness support in notifier mode
2025-05-31 led update fix
2025-06-03 fix GXXX
2025-06-03 MQTT integration for home assistant
2025-06-03 show state in homeassistant, added hhmmss time
2025-06-03 mqtt_bridge_v1.2
2025-06-03 seconds mqtt_bridge_v1.3
    Changes Made:
    MQTT_BROKER = "rpi2": Updated as requested.
    Time Format in display_manager_thread_func:
    time_str_for_badge = time.strftime("%H%M%S")
    badge_time_display = time_str_for_badge
    IGNORE_WHEN_COPYING_START
2025-06-03 precise seconds update
    analyze timestamps from output step by step, especially sencods update which is not 100% correct and updated each second. if you time duration of update each second and substract that from wait for a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
2025-06-04 fix ctrl+c exit
2025-06-04 whitespace diff?
2025-06-04 think mqtt_bridge_v1.4
2025-06-04 minimum changes
2025-06-04 PWM command: P<char_idx><seg_idx><pwm_value>
2025-06-04 fix from gemini (grok generated solution was not good enough :-)
2025-06-25 feat: Implement robust MQTT bridge for conference badge
    This commit introduces a complete, multi-threaded Python script to act as an MQTT bridge for the DC2025 conference badge, enabling full control and event handling via Home Assistant.
    The script was developed and refined through an iterative process, addressing several bugs, race conditions, and inefficiencies to arrive at this stable and feature-complete version.
    Key Features & Fixes:
    - **Full Button Event Handling:**
    - Implements a dedicated, non-blocking `serial_reader_thread` to listen for incoming data from the badge without impacting display timing.
    - Parses the specific firmware event format (`#BTN::{index}::{type}$`) to co
